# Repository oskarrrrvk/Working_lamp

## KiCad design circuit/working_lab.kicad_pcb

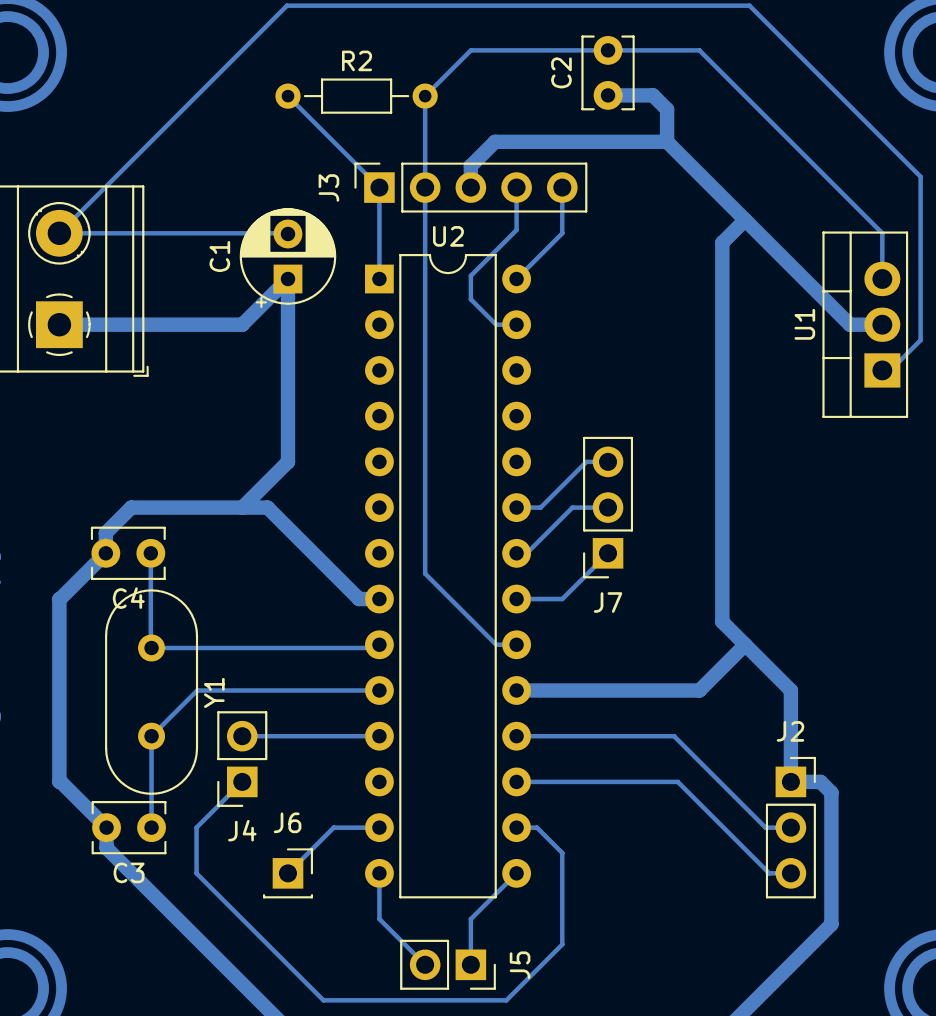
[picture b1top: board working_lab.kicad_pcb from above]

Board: 2 copper layers, 15 parts (0 on the bottom side), 18 nets.

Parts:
C1: 0.33uF; CP_Radial_D5.0mm_P2.50mm
C2: 0.1uF; C_Disc_D3.8mm_W2.6mm_P2.50mm
C3, C4: 22pF; C_Disc_D3.8mm_W2.6mm_P2.50mm
J1: Screw_Terminal_01x02; TerminalBlock_Phoenix_MKDS-1,5-2-5.08_1x02_P5.08mm_Horizont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
J2: UART; PinSocket_1x03_P2.54mm_Vertical
J3: PIC_KIT; PinSocket_1x05_P2.54mm_Vertical
J4: SPI; PinSocket_1x02_P2.54mm_Vertical
J5: I2C; PinSocket_1x02_P2.54mm_Vertical
J6: PWM; PinSocket_1x01_P2.54mm_Vertical
J7: Analogic; PinSocket_1x03_P2.54mm_Vertical
R2: 5K; R_Axial_DIN0204_L3.6mm_D1.6mm_P7.62mm_Horizontal
U1: L7805; TO-220-3_Vertical
U2: PIC16F886-IP; DIP-28_W7.62mm
Y1: 2MHz; Crystal_HC18-U_Vertical

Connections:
+12V: C1.2, J1.2, U1.1 (IN)
GND: C1.1, C2.1, C3.2, C4.2, J1.1, J2.1, J3.3, U1.2 (GND), U2.8 (VSS), U2.19 (VSS)
ICSPCLK: J3.4, U2.27 (ICSPCLK/RB6)
ICSPDAT: J3.5, U2.28 (ICSPDAT/RB7)
unnamed: J5.1, U2.15 (RC4/SDI/SDA)
unnamed: J5.2, U2.14 (RC3/SCK/SCL)
unnamed: J6.1, U2.13 (RC2/P1A/CCP1)
unnamed: J7.1, U2.21 (INT/AN12/RB0)
unnamed: J7.2, U2.22 (P1C/AN10/RB1)
unnamed: J7.3, U2.23 (P1B/AN8/RB2)
unnamed: C4.1, U2.9 (CLKIN/OSC1/RA7), Y1.1
unnamed: C3.1, U2.10 (CLKOUT/OSC2/RA6), Y1.2
VDD: C2.2, J3.2, R2.2, U1.3 (OUT), U2.20 (VDD)
clk: J4.2, U2.11 (RC0/T1OSO/T1CK1)
dataOUT: J4.1, U2.16 (RC5/SDO)
mclr: J3.1, R2.1, U2.1 (RE3/~MCLR/Vpp)
rx: J2.2, U2.18 (RC7/RX/DT)
tx: J2.3, U2.17 (RC6/TX/CK)

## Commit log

2023-10-26 proyect created
2023-10-27 circuit scheme created
2023-11-03 circuit in progress
2023-11-08 I2C connection in circuit created
2023-11-09 connections update
2023-11-09 circuit update
2023-11-09 circuit completed
2023-11-09 completed circuit
2023-11-10 first version of the circuit and starting code
2023-11-29 lamp modified diagram completed
2023-11-29 turn on and off diagrams
2023-11-30 SMA state diagram modified
2023-11-30 diagrams_completed
2023-11-30 last changes diagrams
2023-12-22 smart lamp completed
